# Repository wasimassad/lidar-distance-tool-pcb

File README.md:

# LiDAR Distance Measuring Tool – PCB Design

Senior Design Project  
University of Wisconsin–Milwaukee  

This repository contains the complete PCB design files for the LiDAR Distance Measuring Tool.  
All boards were designed using KiCad.

---

## 📌 Project Overview

This system consists of three custom printed circuit boards:

### 🔹 PCB1 – Power Board
Handles AC/DC conversion and voltage regulation.

### 🔹 PCB2 –  Battery Charging Circuitry
Comprises the battery charging IC for proper, stable, and fast charging of the Li-po battery. Also contains the 5V and 3.3V regulators for the necessary power rails.

### 🔹 PCB3 – Main Control Board / Sensor Board
Contains the microcontroller, LiDAR module, display connections, and integrated sensors.

---

## 🛠 Software Used

- KiCad 9.0

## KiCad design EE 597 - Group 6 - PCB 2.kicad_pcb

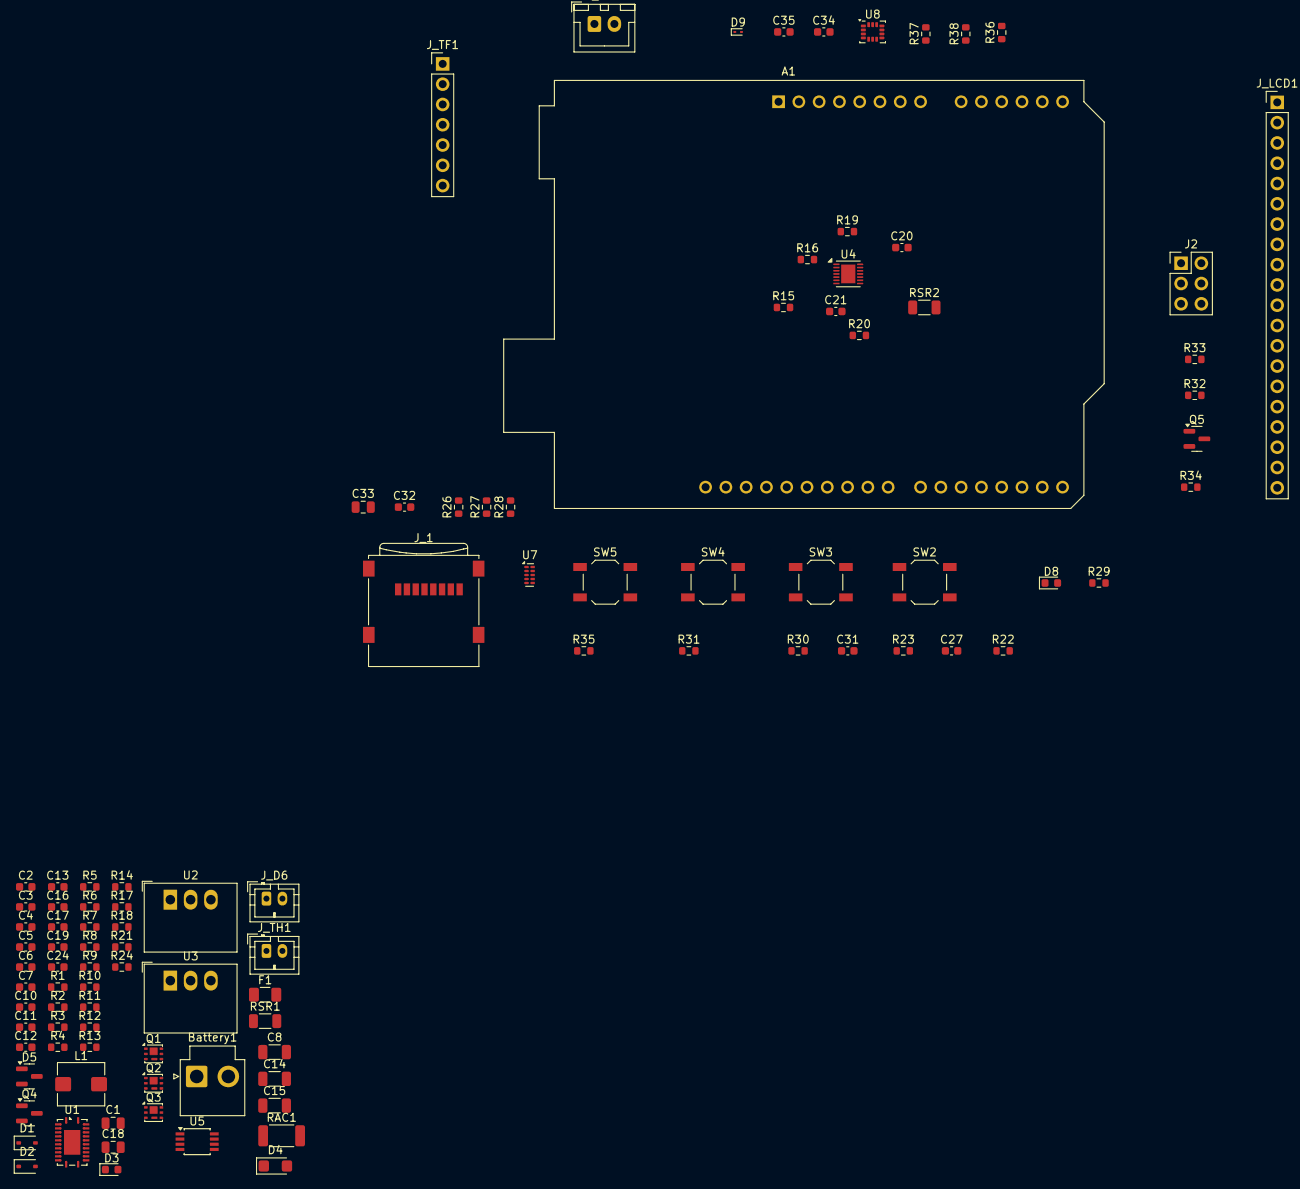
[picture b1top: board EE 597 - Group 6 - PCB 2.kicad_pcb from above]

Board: 2 copper layers, 101 parts (0 on the bottom side), 58 nets, no tracks yet.

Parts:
A1: Arduino_UNO_R3
Battery1: 12V; JST_VH_B2P-VH-B_1x02_P3.96mm_Vertical
C1: 2.2µF; C_0805_2012Metric
C2, C4, C12: 1µF; C_0603_1608Metric
C3, C5, C6, C7, C10, C11, C13, C27, C31, C32, C34, C35: 0.1µF; C_0603_1608Metric
C8, C14, C15: 10µF; C_1206_3216Metric
C16, C17, C19, C20: 0.1μF; C_0603_1608Metric
C18: 10μF; C_0805_2012Metric
C21: 0.47μF; C_0603_1608Metric
C24: 47pF; C_0603_1608Metric
C33: 10µF; C_0805_2012Metric
D1, D2: 1N4148WS; D_SOD-323
D3, D8: G_LED; LED_0603_1608Metric
D4: SMF5V0A; D_SMF
D5: SP0502BAHTG; SOT-23
D9: ESD9B3.3ST5G; D_SOD-923
F1: 1206L035; Fuse_1206_3216Metric
J2: SPI Connector; PinHeader_2x03_P2.54mm_Vertical
J_1: Micro_SD_Card; microSD_HC_Wuerth_693072010801
J_D6: BPW34; JST_PH_B2B-PH-K_1x02_P2.00mm_Vertical
J_LCD1: Conn_01x20; PinHeader_1x20_P2.54mm_Vertical
J_SW1: SW_SPST; JST_XH_B2B-XH-A_1x02_P2.50mm_Vertical
J_TF1: Conn_01x07; PinHeader_1x07_P2.54mm_Vertical
J_TH1: 10kΩ; JST_PH_B2B-PH-K_1x02_P2.00mm_Vertical
L1: 3.3µH; L_Bourns_SRP5030T
Q1, Q2: CSD17313Q2; Texas_DQK
Q3: CSD25310Q2; Texas_DQK
Q4, Q5: AO3400A; SOT-23
R1: 10Ω; R_0603_1608Metric
R2: 2Ω; R_0603_1608Metric
R3: 323kΩ; R_0603_1608Metric
R4: 34kΩ; R_0603_1608Metric
R5, R12, R18, R33: 100kΩ; R_0603_1608Metric
R6: 47kΩ; R_0603_1608Metric
R7: 5.23kΩ; R_0603_1608Metric
R8: 30.1kΩ; R_0603_1608Metric
R9, R10: 4kΩ; R_0603_1608Metric
R11, R29: 240Ω; R_0603_1608Metric
R13: 17.8kΩ; R_0603_1608Metric
R14, R24: 1kΩ; R_0603_1608Metric
R15: 1.3MΩ; R_0603_1608Metric
R16: 200kΩ; R_0603_1608Metric
R17, R32: 100Ω; R_0603_1608Metric
R19, R20, R21, R22, R26, R27, R28, R30, R31, R35, R36, R37, R38: 10kΩ; R_0603_1608Metric
R23: 330Ω; R_0603_1608Metric
R34: 22Ω; R_0603_1608Metric
RAC1: 0.02Ω; R_2010_5025Metric
RSR1, RSR2: 0.01Ω; R_1206_3216Metric
SW2, SW3, SW4, SW5: SW_Push; SW_SPST_TL3342
U1: BQ24133RGY; Texas_RGY_R-PVQFN-N24_EP2.05x3.1mm
U2: R-78B5.0-2.0; Converter_DCDC_RECOM_R-78B-2.0_THT
U3: R-78B3.3-2.0; Converter_DCDC_RECOM_R-78B-2.0_THT
U4: MAX17261xxTD; TDFN-14-1EP_3x3mm_P0.4mm_EP1.78x2.35mm
U5: TLV9002; TSSOP-8_3x3mm_P0.65mm
U7: TPD4E05U06DQA; USON-10_2.5x1.0mm_P0.5mm
U8: LSM6DSOTR; LGA-14_3x2.5mm_P0.5mm_LayoutBorder3x4y

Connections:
/VBAT: Battery1.1 (+), C11.2, C13.2, C14.2, C15.2, D1.2 (A), Q3.4 (D), Q3.7 (D), R15.1, RSR1.2, U1.15 (SRN)
/VREF: C2.2, R5.1, R7.1, R11.1, R12.1, U1.12 (VREF), U1.14 (CELL)
GND: A1.6 (GND), Battery1.2 (-), C1.1, C2.1, C3.1, C4.1, C5.1, C7.2, C8.2, C10.1, C11.1, C12.1, C14.1, C15.1, C16.1, C17.1, C18.2, C19.1, C20.2, C21.2, C27.2, C31.2, C32.2, C33.2, C34.2, C35.2, D4.2 (A2), D5.3 (A), D8.1 (K), D9.1 (A1), J2.6, J_1.6 (VSS), J_1.9 (SHIELD), J_D6.2 (A), J_LCD1.1, J_LCD1.14, J_TF1.7, J_TH1.2, Q4.2 (S), Q5.2 (S), R4.2, R6.2, R8.2, R13.2, R16.2, R18.1, R30.1, R31.1, R33.1, R35.1, RSR2.1, RSR2.2, SW2.1, U1.22 (PGND), U1.23 (PGND), U1.25 (AGND), U2.2 (GND), U3.2 (GND), U4.7 (CSN), U4.8 (GND), U4.9 (CSPL), U4.12 (ALRT), U4.15 (GND), U5.3 (+), U5.4 (V-), U7.3 (GND), U7.8 (GND), U8.1 (SDO/SA0), U8.6 (GND), U8.7 (GND)
unnamed: A1.9 (A0), R24.2
unnamed: A1.15 (D0/RX), D5.1 (K), J_TF1.5
unnamed: A1.16 (D1/TX), D5.2 (K), J_TF1.6
unnamed: A1.17 (D2), R17.1
unnamed: A1.18 (D3), J_1.2 (DAT3/CD), R28.2, U7.1 (D1+)
unnamed: A1.19 (D4), J_LCD1.11
unnamed: A1.20 (D5), R29.1
unnamed: A1.21 (D6), R30.2, SW3.2
unnamed: A1.22 (D7), R31.2, SW4.2
unnamed: A1.23 (D8), R35.2, SW5.2
unnamed: A1.24 (D9), J_LCD1.12
unnamed: A1.25 (D10), R32.2
unnamed: A1.8 (VIN), C16.2, C17.2, C18.1, D4.1 (A1), F1.2, J_TF1.1
unnamed: A1.3 (~RESET), C27.1, J_LCD1.13, R22.2, R23.2
unnamed: C1.2, R2.1
unnamed: C24.2, R21.2, R24.1, U5.1
unnamed: D1.1 (K), D2.1 (K), R1.1
unnamed: D2.2 (A), Q1.1 (D), Q1.2 (D), Q1.5 (D), Q1.6 (D), Q1.8 (D), R2.2, R3.1
unnamed: D3.2 (A), R11.2
unnamed: D3.1 (K), U1.9 (STAT)
unnamed: D8.2 (A), R29.2
unnamed: C19.2, C20.1, C31.1, C34.1, C35.1, D9.2 (A2), J_LCD1.6, J_LCD1.7, J_LCD1.15, R19.1, R20.1, R22.1, R36.1, R37.1, R38.1, SW3.1, SW4.1, SW5.1, U3.3 (OUT), U4.1 (TH), U4.6 (BATT), U5.8 (V+), U8.5 (VDDIO), U8.8 (VDD)
unnamed: J2.1, J_1.7 (DAT0), J_LCD1.9, R26.2, U7.5 (D2-)
unnamed: J2.3, J_1.5 (CLK), J_LCD1.10, U7.4 (D2+)
unnamed: J2.4, J_1.3 (CMD), J_LCD1.8, R27.2, U7.2 (D1-)
unnamed: C32.1, C33.1, J_1.4 (VDD), J_SW1.2 (B), R26.1, R27.1, R28.1, U2.1 (IN), U3.1 (IN)
unnamed: C24.1, J_D6.1 (K), R21.1, U5.2 (-)
unnamed: J_LCD1.16, J_LCD1.17, J_LCD1.18, J_LCD1.19, Q5.3 (D)
unnamed: J_LCD1.20, R34.1
unnamed: C6.2, C7.1, C8.1, J_SW1.1 (A), Q3.1 (S), Q3.2 (S), Q3.5 (S), Q3.6 (S), Q3.8 (S), RAC1.2, U1.2 (PVCC), U1.3 (PVCC), U1.5 (ACN)
unnamed: L1.1, U1.1 (SW), U1.24 (SW)
unnamed: Q1.3 (G), Q2.3 (G), R10.1
unnamed: Q1.4 (S), Q1.7 (S), Q2.4 (S), Q2.7 (S), R9.1
unnamed: Q3.3 (G), R14.2
unnamed: Q4.1 (G), R17.2, R18.2
unnamed: Q5.1 (G), R32.1, R33.2
unnamed: R23.1, SW2.2
unnamed: R10.2, U1.8 (ACDRV)
unnamed: C3.2, C6.1, Q2.1 (D), Q2.2 (D), Q2.5 (D), Q2.6 (D), Q2.8 (D), RAC1.1, U1.6 (ACP)
unnamed: R5.2, R6.1, U1.17 (ACSET)
unnamed: C4.2, R1.2, U1.4 (AVCC)
unnamed: R9.2, U1.7 (CMSRC)
unnamed: R12.2, R13.1, U1.13 (ISET)
unnamed: R3.2, R4.1, U1.18 (OVPSET)
unnamed: C12.2, U1.20 (REGN)
unnamed: C10.2, C13.1, L1.2, RSR1.1, U1.16 (SRP)
unnamed: J_TH1.1, R7.2, R8.1, U1.10 (TS)
unnamed: C5.2, U1.11 (TTC)
unnamed: R14.1, U1.19 (~BATDRV)
unnamed: F1.1, R34.2, U2.3 (OUT)
unnamed: R15.2, R16.1, U4.10 (CELLX)
unnamed: C21.1, U4.11 (REG)
unnamed: A1.14 (SCL/A5), R19.2, R37.2, U4.14 (SCL), U8.13 (SCL)
unnamed: A1.13 (SDA/A4), R20.2, R36.2, U4.13 (SDA), U8.14 (SDA)
unnamed: R38.2, U8.12 (CS)

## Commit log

2026-02-16 Initial PCB repo structure + KiCad projects
2026-02-16 Keep Pcb folder in repo
2026-02-16 Add PCB board folders
2026-02-17 no traces
2026-02-19 Edge made, begin traces
2026-02-20 Sending off to priyansh
